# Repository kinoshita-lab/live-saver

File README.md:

# What?
Live Saver is a passive diode(LED) clipper to limit input signal to approx. +4dBu(=+- 1.73V), actual +- 1.75V with Vf specification of the diodes.

Both inputs and outputs are 3.5mm TRS, can use for stereo signal.

# Usage Example
The main objective for this product is to avoid destroying PA system with (elementary, primitive) DIY electronic instruments without protection circuit.

Also can be used as a fixed diode clipper.

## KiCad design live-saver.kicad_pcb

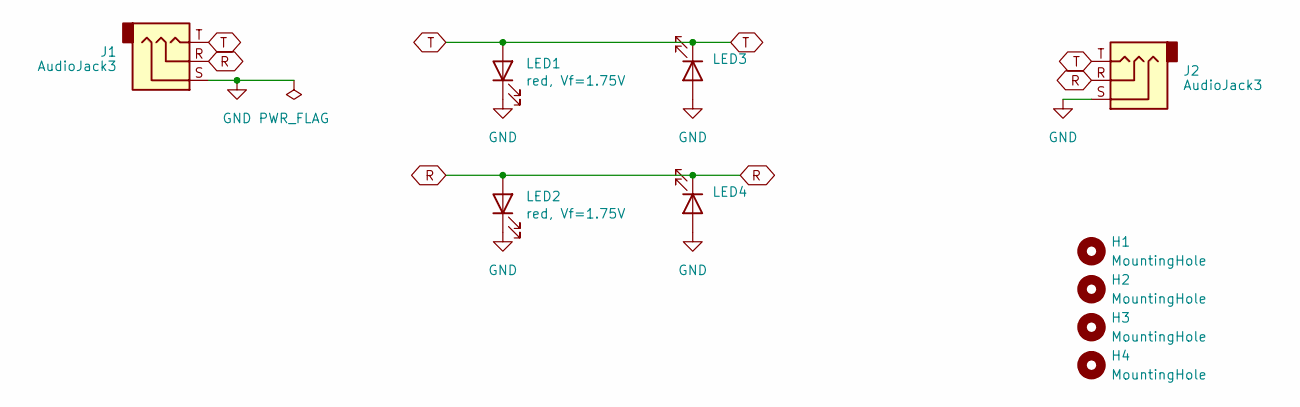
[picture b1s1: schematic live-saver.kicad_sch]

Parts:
H1, H2, H3, H4: MountingHole; MountingHole_2.2mm_M2_DIN965
J1, J2: AudioJack3; 3.5mm_Stereo_TRS_PJ-3210-4A_and_ST-005-G; LCSC C136686
LED1, LED2, LED3, LED4: red, Vf=1.75V; LED_0603_1608Metric_Pad1.05x0.95mm_HandSolder; LCSC C79636

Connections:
GND: J1.S, J2.S, LED1.1 (K), LED2.1 (K), LED3.2 (A), LED4.2 (A)
R: J1.R, J2.R, LED2.2 (A), LED4.1 (K)
T: J1.T, J2.T, LED1.2 (A), LED3.1 (K)

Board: 2 copper layers, 10 parts (0 on the bottom side), 3 nets, no tracks yet.
